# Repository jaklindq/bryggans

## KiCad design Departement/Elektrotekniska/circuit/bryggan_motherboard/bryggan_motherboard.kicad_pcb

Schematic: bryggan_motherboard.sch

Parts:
J1: RJ12; RJ12_E
J2: Screw_Terminal_01x07; TerminalBlock_Phoenix_PT-3.5mm_7pol
J3: Barrel_Jack; BARREL_JACK
P3: Raspberry_Pi_+_Conn; Pin_Header_Straight_2x20_Pitch2.54mm; Mouser Part No. 517-30340-6002
R1: 4.7k; R_Axial_DIN0207_L6.3mm_D2.5mm_P7.62mm_Horizontal
U1: ULN2003A; DIP18

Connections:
+5V: J3.1, U1.9 (COM); also elsewhere on the board
/+3.3V: J1.3, J1.4, P3.17, R1.1
/Back Power Protection/5V_MCU: P3.2, P3.4; also elsewhere on the board
/FAN_GPIO_16: P3.36, U1.4 (I4)
/GPIO_20: P3.38, U1.2 (I2)
/GPIO_21: P3.40, U1.1 (I1)
/GPIO_26: P3.37, U1.3 (I3)
/HEAT_GPIO_13_PWM: P3.12, U1.7 (I7)
/PUMP1_GPIO_18_PWM: P3.33, U1.6 (I6)
/PUMP2_GPIO_19: P3.35, U1.5 (I5)
/TEMP_GPIO_4: J1.1, J1.2, P3.7, R1.2
GND: J1.5, J1.6, J3.2, P3.20, U1.8 (GND); also elsewhere on the board
unnamed: J2.1, U1.10 (O7)
unnamed: J2.2, U1.11 (O6)
unnamed: J2.3, U1.12 (O5)
unnamed: J2.4, U1.13 (O4)
unnamed: J2.5, U1.14 (O3)
unnamed: J2.6, U1.15 (O2)
unnamed: J2.7, U1.16 (O1)

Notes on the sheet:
Raspberry Pi Connection
Transistor array
Thermometer connect

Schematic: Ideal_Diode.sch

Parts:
Q1: BSS138; sot23; Mouser Part No. 621-DMG2305UX-13
R11: 10k; R_Axial_DIN0207_L6.3mm_D2.5mm_P7.62mm_Horizontal; Mouser Part No. 71-CRCW0402-10K-E3
R12: 47k; R_Axial_DIN0207_L6.3mm_D2.5mm_P7.62mm_Horizontal; Mouser Part No. 667-ERJ-2RKF4702X
U5: DMMT5401; sot23-6; Mouser Part No. 621-DMMT5401-7-F

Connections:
+5V: Q1.3, U5.6; also elsewhere on the board
/Back Power Protection/5V_MCU: Q1.2, U5.5; also elsewhere on the board
GND: R11.2, R12.2; also elsewhere on the board
unnamed: Q1.1, R12.1, U5.4
unnamed: R11.1, U5.1, U5.2, U5.3

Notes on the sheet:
*Recomended back powering protection for raspberry pi. Recomended by Raspberyy Pi Foundation https://github.com/raspberrypi/hats/blob/master/designguide.md

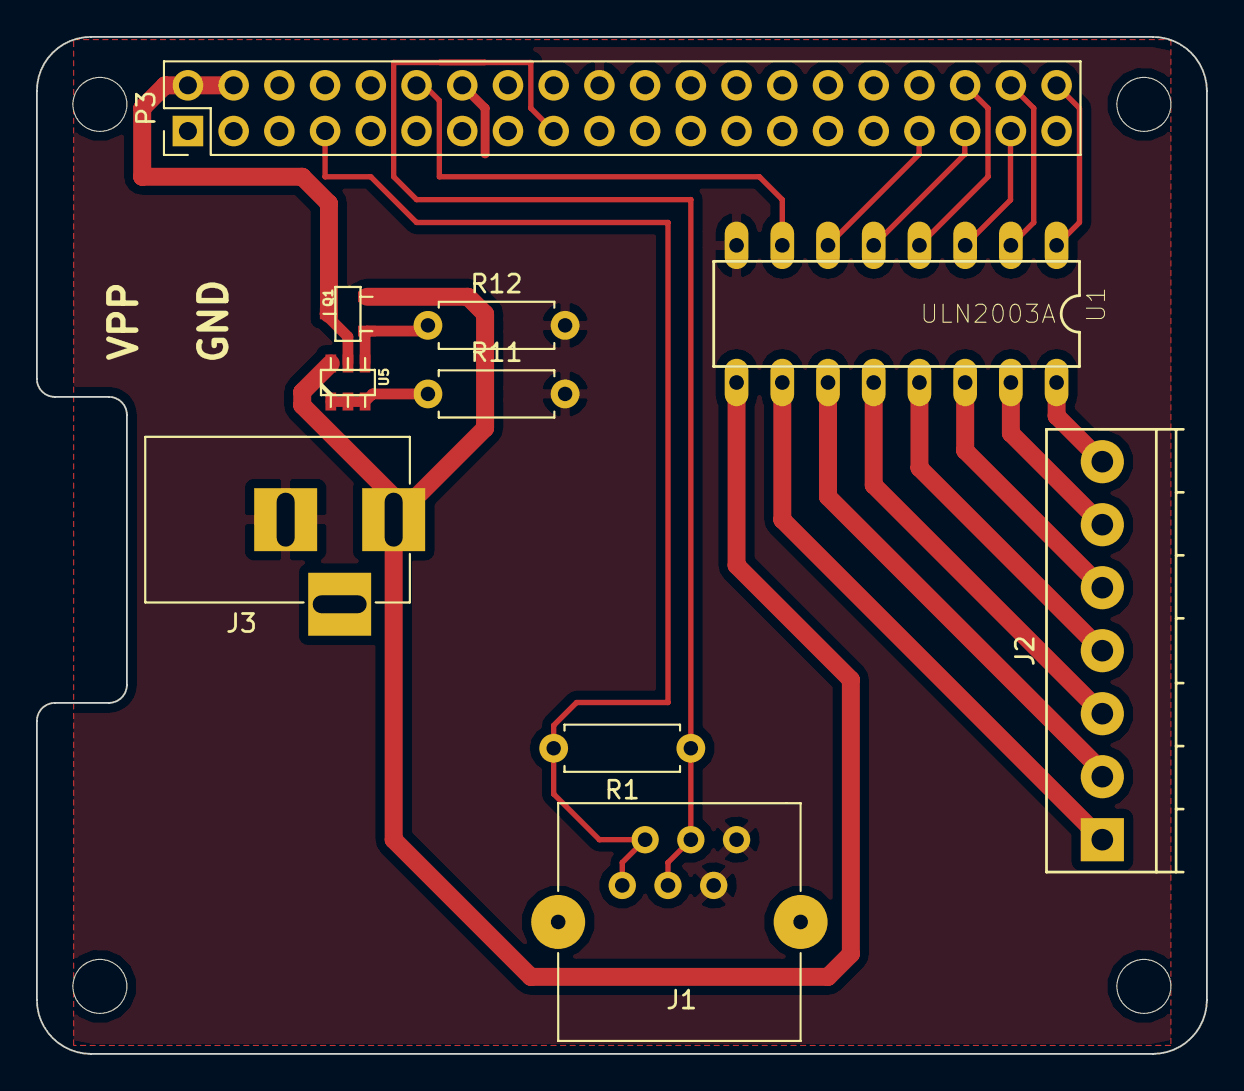
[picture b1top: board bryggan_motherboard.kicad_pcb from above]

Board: 2 copper layers, 65.0 x 56.5 mm, 10 parts (0 on the bottom side), 21 nets.

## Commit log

2017-09-11 Added recipes for tracking
2017-09-23 Two recipes
2018-02-25 beerSmith changes
2018-02-26 Added beersmith folder
2018-02-26 Added first Technical Drawing
2018-02-28 Add 2 recipe
2018-02-28 Add xml file format to previous recipes
2018-03-01 Computer switch
2018-03-01 Peristaltic pump initial commit
2018-03-01 Tracking blockposts
2018-03-01 Coherent file structure
    Too many subdirs with Mekaniska/Project/Project_dir
    Now Mekaniska/Project_dir
2018-03-01 Separate dir for xml-recipes
2018-03-01 Recipe module init
2018-03-01 Updated version tags in bxml
    Lipa 1.0 --> 4.0
    Kalaslager 1 --> 2
2018-03-02 Unit conversion
2018-03-02 Added Darlington array datasheet for posterity
2018-03-02 Removed useless(?) beersmith files
2018-03-02 Pump python embryo
2018-03-02 Added docs
2018-03-02 Pump drawings
2018-03-02 gitignore
2018-03-02 Legacy recipes
2018-03-02 Oz conversion and unit check embryo
2018-03-03 OG and date for APA, WIP
2018-03-04 Updated recipes
2018-03-12 Added transistor array datasheet
2018-03-12 OG for kalaslager
2018-03-13 Docker+flask
2018-03-13 Hello world with Flask + docker working
    Some trailing fixes though, I can't seem to get the output ported
    without the -it flag and building the container without entrypoint
2018-03-13 Fixed last subissue
2018-03-13 Ignoring readme renders
2018-03-13 Fixed mounting problem
    See README.md for running info
2018-03-13 Fixed mount
2018-03-15 Intermediate commit for Jontis eyes only
    Will refactor soon!
2018-03-16 Added ginger beer recipe, NOT COMPLETED
2018-05-06 Motherboard first rev
2018-05-24 Non-important info format
2018-05-24 Fixed type check with .get()
2018-05-24 Embryo for Ingredient (better class inheteritance)
2018-05-25 Nicer keywors
2018-05-25 Restructuring recipe module
    Adding abstract class Ingredient w/ common attributes:
    Name, amount (more to be added)
    Good for xml-parsing since all ingredient share some properties
    Also valid as an interface for new ingredients
2018-05-25 Generic add_ingred list
2018-05-25 Fixed type check sum_list
2018-05-25 Sep src dir
2018-05-25 Logging implemented
2018-05-25 More generic logging
2018-06-13 Ignore more
2018-07-11 Mark 0.1 brew enclosure
    All connections made except for switches and indicators
    Debugged, only error is passive/active conflict for neutral AC
2018-07-11 Motherboard file structure
    Complied to good practice
    No actual changes
2018-07-11 Kicad ignores
2018-07-11 One neutral per group
2018-07-11 Removed scrap parts
2018-07-12 OG ginger recipe
2018-07-12 Store recipe
2018-07-25 KICAD clean
2018-07-25 Web recipe ammend
2018-07-25 RAW PIHAT TEMPLATE REMAKE
    Template taken from: https://www.instructables.com/id/Design-a-Raspberry-Pi-Hat-KiCad/
    No changes made, except replacing outdated components
2018-07-25 Components added to board
    Schematic RbPi to component fixed. No outgoing to full enclosure
2018-07-27 Tracking almost done
2018-07-28 Trans array footprint and wiring
2018-07-29 PCB v0.9 finished
    - Ground plane
    - Barrel jack
    - All tracks
    - PCBNew Error check OK
2018-08-07 fine lire
2018-08-07 START "GJELLEGRAS" - AUTOMATIC HOPS IRRIGATION
    Rudimentary kicad schematics. Not ment for pcb at this stage, wiring
    schematics only.
2018-10-19 Started pipenv, not convinced yet
2018-10-19 Ordning och reda i recept
2018-10-19 Started Model predictive control
2018-10-22 Security alert
    Updated flask version required
2018-11-13 Transfer pending Bryggan180.0

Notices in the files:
Departement/Elektrotekniska/circuit/bryggan_motherboard/bryggan_motherboard.kicad_pcb:
License: CERN OHL V1.2
CERN OHL V1.2
